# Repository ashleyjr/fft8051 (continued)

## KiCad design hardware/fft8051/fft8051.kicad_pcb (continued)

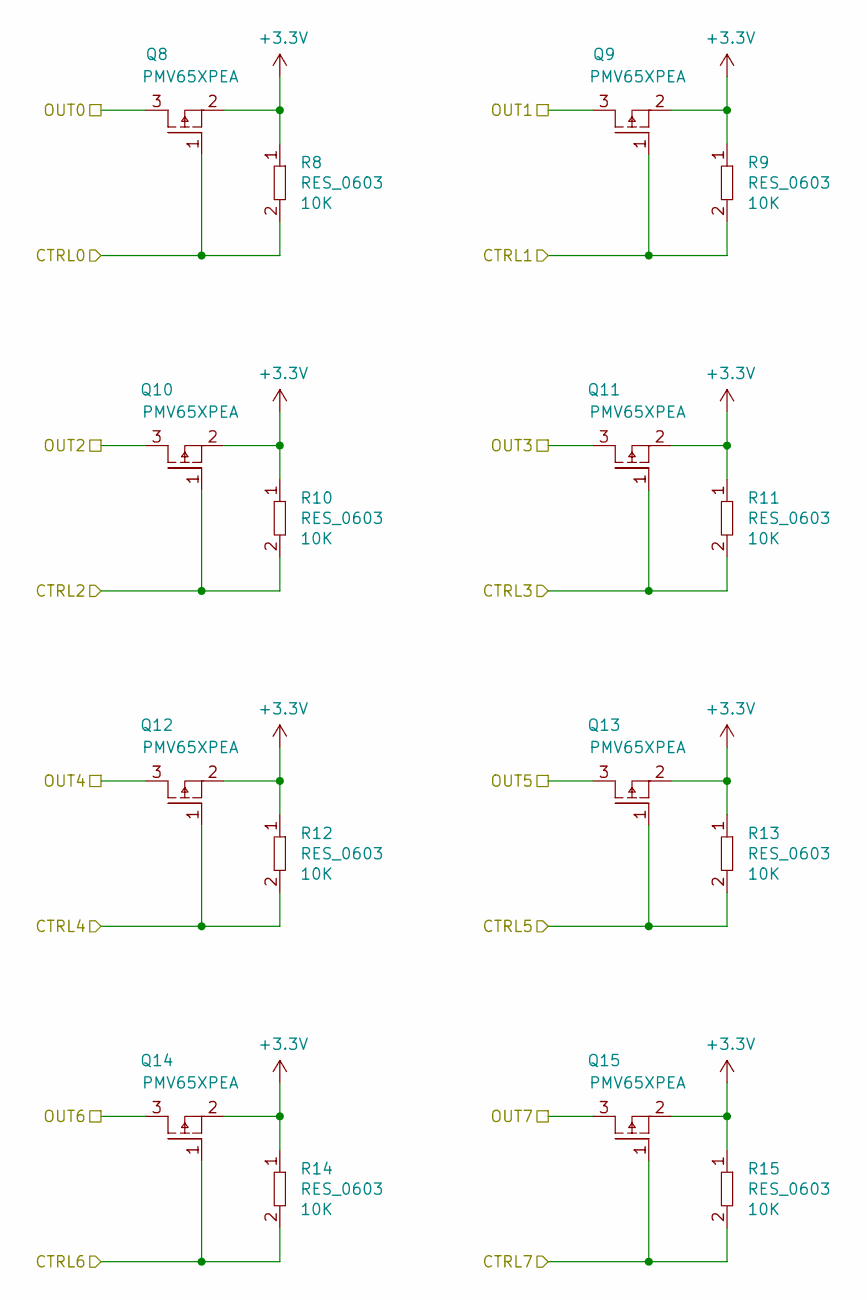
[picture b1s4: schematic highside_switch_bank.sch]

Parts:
Q0, Q1, Q2, Q3, Q4, Q5, Q6, Q7: PMV65XPEA
R0, R1, R2, R3, R4, R5, R6, R7: RES_0603; 0603

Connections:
+3V3: Q0.2, Q1.2, Q2.2, Q3.2, Q4.2, Q5.2, Q6.2, Q7.2, R0.1, R1.1, R2.1, R3.1, R4.1, R5.1, R6.1, R7.1; also elsewhere on the board
/Sheet5F08D406/Sheet5EE72AD5/0: Q0.3; also elsewhere on the board
/Sheet5F08D406/Sheet5EE72AD5/1: Q1.3; also elsewhere on the board
/Sheet5F08D406/Sheet5EE72AD5/2: Q2.3; also elsewhere on the board
/Sheet5F08D406/Sheet5EE72AD5/3: Q3.3; also elsewhere on the board
/Sheet5F08D406/Sheet5EE72AD5/4: Q4.3; also elsewhere on the board
/Sheet5F08D406/Sheet5EE72AD5/5: Q5.3; also elsewhere on the board
/Sheet5F08D406/Sheet5EE72AD5/6: Q6.3; also elsewhere on the board
/Sheet5F08D406/Sheet5EE72AD5/7: Q7.3; also elsewhere on the board
/Sheet5F08D406/Sheet5F05EF8E/CTRL0: Q0.1, R0.2; also elsewhere on the board
/Sheet5F08D406/Sheet5F05EF8E/CTRL1: Q1.1, R1.2; also elsewhere on the board
/Sheet5F08D406/Sheet5F05EF8E/CTRL2: Q2.1, R2.2; also elsewhere on the board
/Sheet5F08D406/Sheet5F05EF8E/CTRL3: Q3.1, R3.2; also elsewhere on the board
/Sheet5F08D406/Sheet5F05EF8E/CTRL4: Q4.1, R4.2; also elsewhere on the board
/Sheet5F08D406/Sheet5F05EF8E/CTRL5: Q5.1, R5.2; also elsewhere on the board
/Sheet5F08D406/Sheet5F05EF8E/CTRL6: Q6.1, R6.2; also elsewhere on the board
/Sheet5F08D406/Sheet5F05EF8E/CTRL7: Q7.1, R7.2; also elsewhere on the board

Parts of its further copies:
Q8, Q9, Q10, Q11, Q12, Q13, Q14, Q15: PMV65XPEA
R8, R9, R10, R11, R12, R13, R14, R15: RES_0603; 0603

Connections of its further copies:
+3V3: Q8.2, Q9.2, Q10.2, Q11.2, Q12.2, Q13.2, Q14.2, Q15.2, R8.1, R9.1, R10.1, R11.1, R12.1, R13.1, R14.1, R15.1; also elsewhere on the board
/Sheet5F08D406/sheet5EEB6AA2/0: Q8.3; also elsewhere on the board
/Sheet5F08D406/sheet5EEB6AA2/1: Q9.3; also elsewhere on the board
/Sheet5F08D406/sheet5EEB6AA2/2: Q10.3; also elsewhere on the board
/Sheet5F08D406/sheet5EEB6AA2/3: Q11.3; also elsewhere on the board
/Sheet5F08D406/sheet5EEB6AA2/4: Q12.3; also elsewhere on the board
/Sheet5F08D406/sheet5EEB6AA2/5: Q13.3; also elsewhere on the board
/Sheet5F08D406/sheet5EEB6AA2/6: Q14.3; also elsewhere on the board
/Sheet5F08D406/sheet5EEB6AA2/7: Q15.3; also elsewhere on the board
/Sheet5F08D406/sheet5F1B74EF/CTRL0: Q8.1, R8.2; also elsewhere on the board
/Sheet5F08D406/sheet5F1B74EF/CTRL1: Q9.1, R9.2; also elsewhere on the board
/Sheet5F08D406/sheet5F1B74EF/CTRL2: Q10.1, R10.2; also elsewhere on the board
/Sheet5F08D406/sheet5F1B74EF/CTRL3: Q11.1, R11.2; also elsewhere on the board
/Sheet5F08D406/sheet5F1B74EF/CTRL4: Q12.1, R12.2; also elsewhere on the board
/Sheet5F08D406/sheet5F1B74EF/CTRL5: Q13.1, R13.2; also elsewhere on the board
/Sheet5F08D406/sheet5F1B74EF/CTRL6: Q14.1, R14.2; also elsewhere on the board
/Sheet5F08D406/sheet5F1B74EF/CTRL7: Q15.1, R15.2; also elsewhere on the board

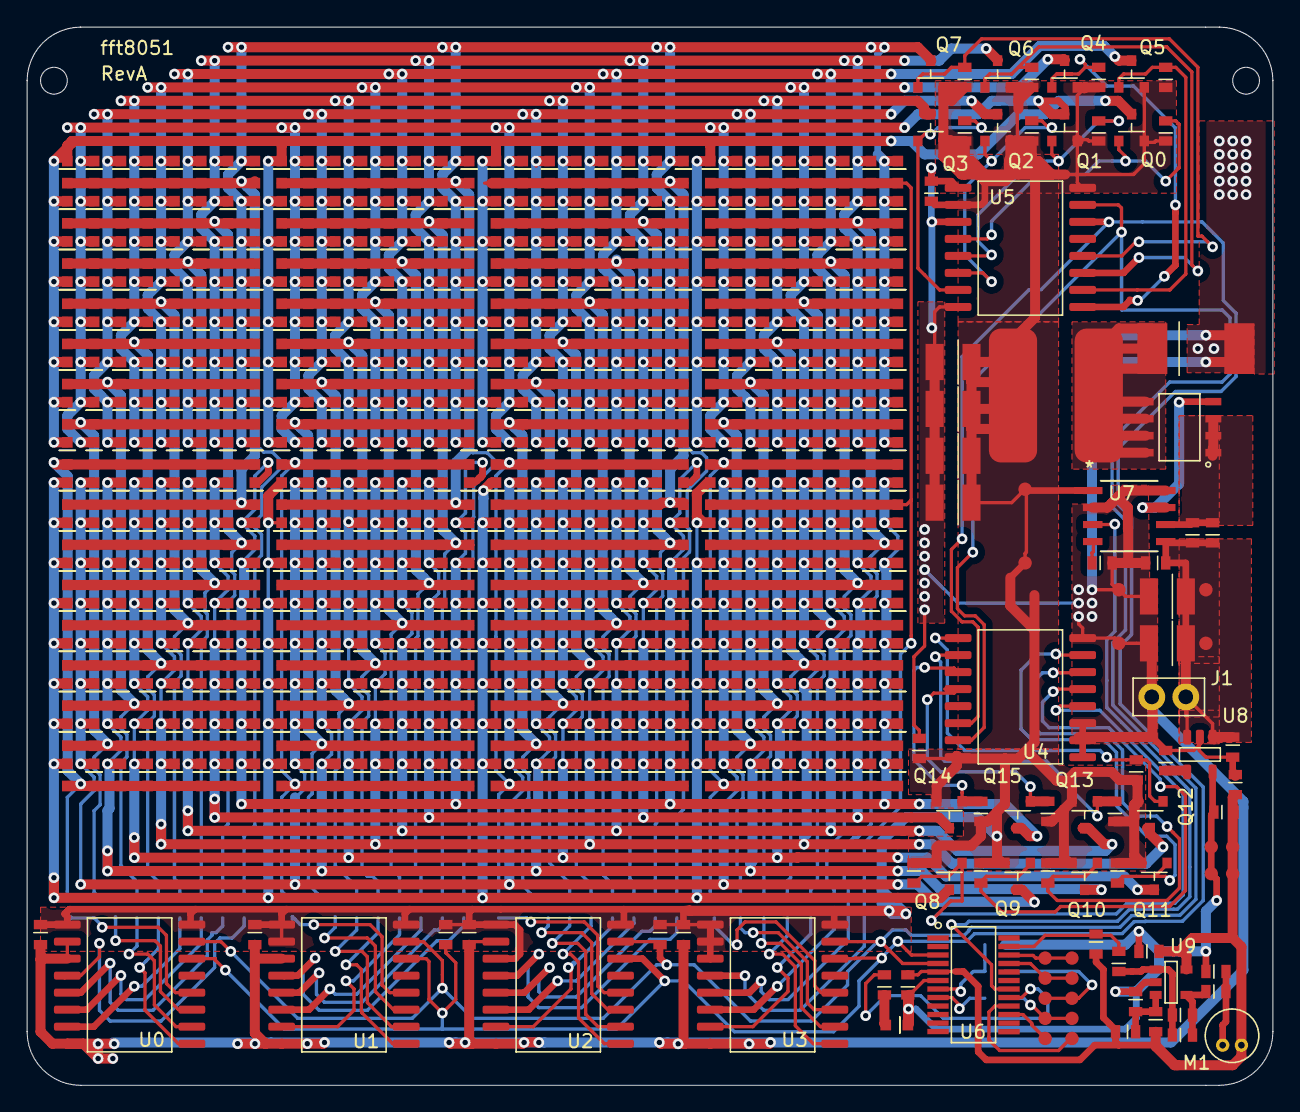
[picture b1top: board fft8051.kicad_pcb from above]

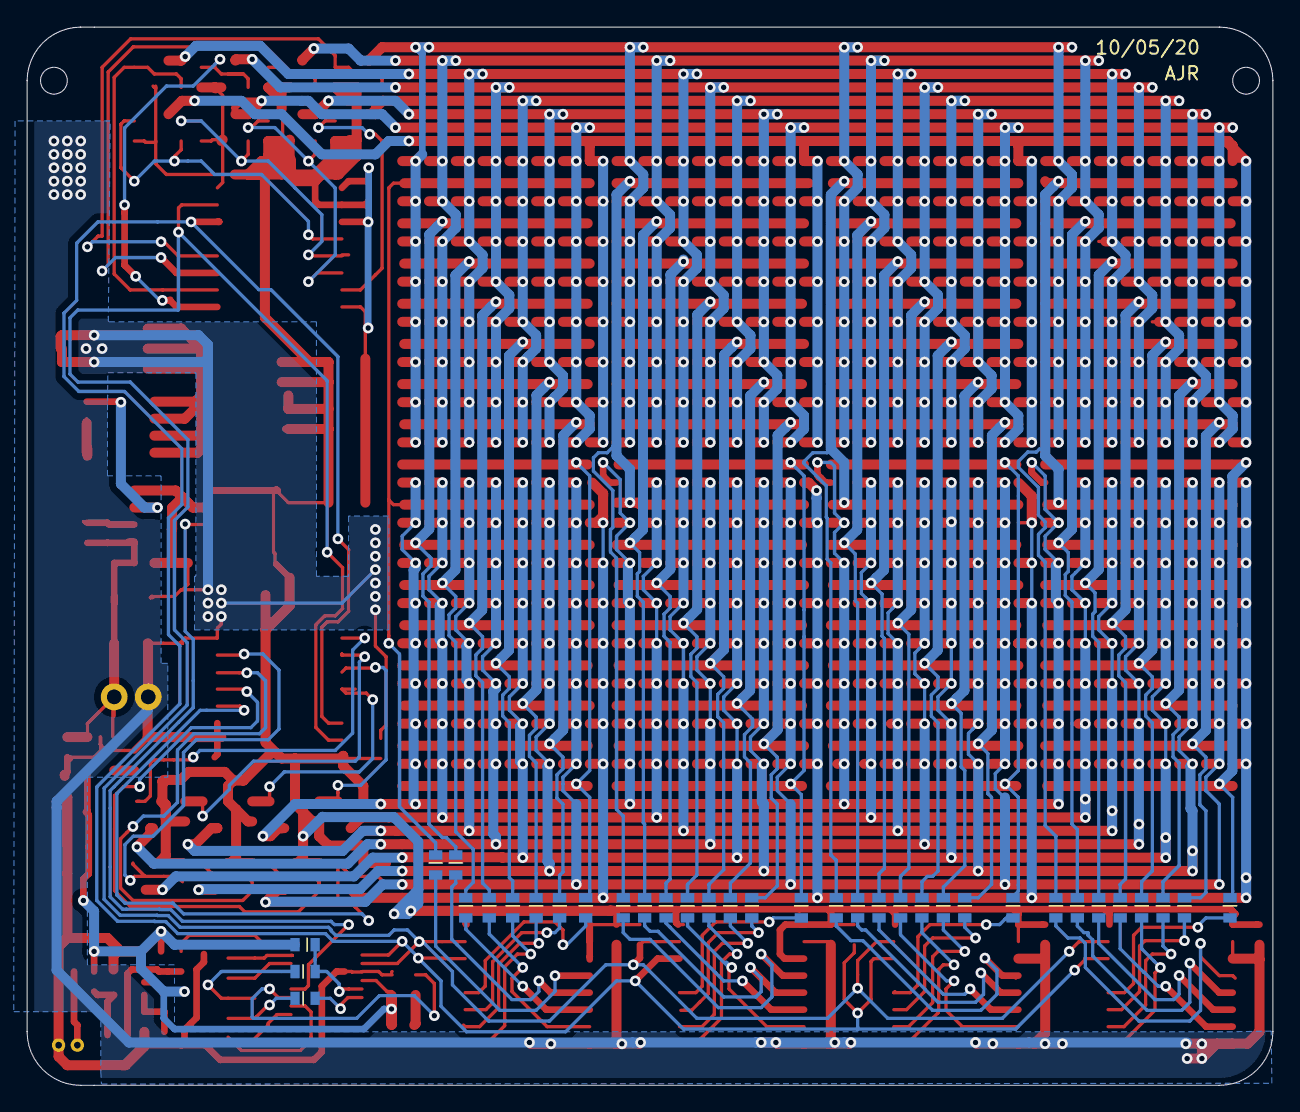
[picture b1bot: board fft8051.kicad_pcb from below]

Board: 2 copper layers, 93.0 x 79.0 mm, 649 parts (35 on the bottom side), 124 nets.

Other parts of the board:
De: MP001249

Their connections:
/Sheet5F08D406/sheet5EE76798/A: De.2; also elsewhere on the board
/Sheet5F08D406/sheet5EEB6AA2/5: De.1; also elsewhere on the board

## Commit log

2020-03-24 Cordic working
2020-03-24 Tidy
2020-03-24 Added clog2
2020-03-25 Created printer
2020-03-25 buffers
2020-03-26 test script
2020-03-27 Buffer test
2020-03-27 Added complex test
2020-03-28 Added reverse test
2020-03-29 Common c for model and uc
2020-03-29 Add twiddle gen
2020-03-29 first model pass
2020-04-01 Plotting fft
2020-04-04 use ints instead of chars
2020-04-05 git ignore file
2020-04-05 More ignores
2020-04-11 FFT working
2020-04-11 ignore pyc
2020-04-12 Streaming test working
2020-04-13 32 out
2020-04-13 Two tests
2020-04-13 Use floats for fft
2020-04-22 Started I2C driver
2020-05-10 fab output
2020-09-20 Full display working
2020-10-02 TEST working
2020-10-03 tidy up image gen
2020-10-24 clean up makefile
2020-10-24 Testing fft display
2020-10-30 plotting bars
2020-11-01 half N display workings
2020-11-08 tidy uart rx
2020-11-08 Remove uart functions
2020-11-08 Using global timer
2020-11-08 fft display working
